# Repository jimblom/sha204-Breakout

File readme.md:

# ATSHA204 Breakout Repository
Here you'll find the hardware design files for the [SparkFun ATSHA204 Breakout](https://www.sparkfun.com/products/11551). You'll also find example Arduino code, including a library for this powerful little chip.

## What's here?
In the *hardware* directory, you'll find the Eagle design files - board and schematic - as well as a pdf version of the schematic.

In the *sha204_library* directory, you'll find the **ATSHA204 Arduino Library** as well as example code to demo what it can do. 

## What is the Atmel ATSHA204?
The Atmel ATSHA204 is an optimized authentication chip that includes a 4.5Kb EEPROM. This array can be used for storage of keys, miscellaneous read/write, read-only, password or secret data, and consumption tracking. Access to the various sections of memory can be restricted in a variety of ways and then the configuration locked to prevent changes.

Each ATSHA204 ships with a guaranteed unique 72-bit serial number. Using the cryptographic protocols supported by the chip, a host system or remote server can prove that the serial number is both authentic and not a copy. The ATSHA204 can generate high-quality random numbers and employ them for any purpose, including usage as part of the crypto protocols of this chip.

Here's a link to the [datasheet](http://www.atmel.com/Images/doc8740.pdf).

- Jim Lindblom @ SparkFun Electronics

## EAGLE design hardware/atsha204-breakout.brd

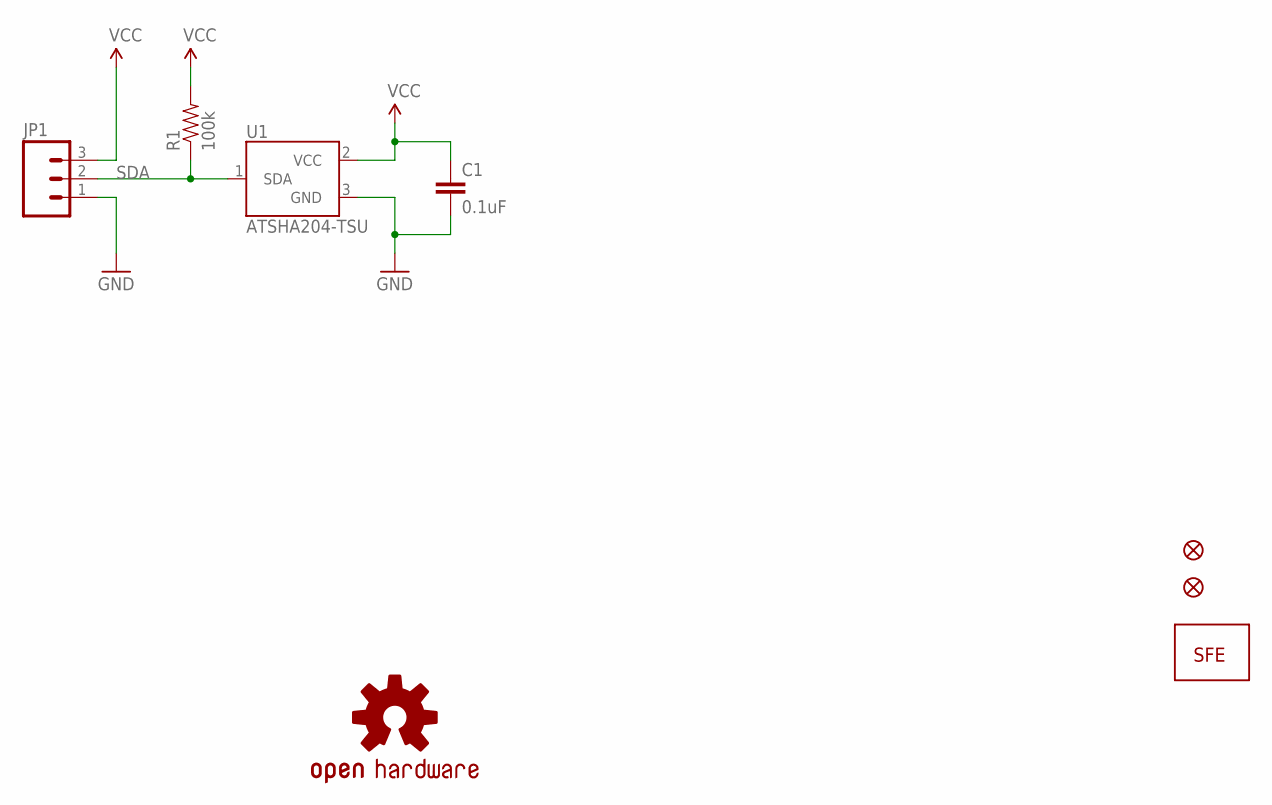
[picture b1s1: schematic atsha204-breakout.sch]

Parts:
C1: 0.1uF; 0402-CAP
JP1: M031X03_NO_SILK; 1X03_NO_SILK
JP2: LOGO-SFESK; SFE-LOGO-FLAME
JP3, JP4: FIDUCIALUFIDUCIAL; MICRO-FIDUCIAL
R1: 100k; 0402-RES
U1: ATSHA204-TSU; SOT23-3
U$1: OSHW-LOGOS; OSHW-LOGO-S

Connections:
GND: C1.2, JP1.1, U1.3 (GND)
SDA: JP1.2, R1.1, U1.1 (SDA)
VCC: C1.1, JP1.3, R1.2, U1.2 (VCC)

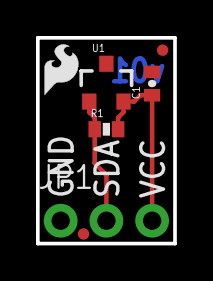
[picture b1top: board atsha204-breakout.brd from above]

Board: 2 copper layers, 7.6 x 11.4 mm, 8 parts (1 on the bottom side), 3 nets.

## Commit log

2012-11-08 Initial commit
    This is an initial working version of the sha204 library and some
    example code using it.
    Also an initial commit of the Eagle design files.
2012-11-08 Revising directory structure
    no need to navigate through all those folders to get to the code.
2012-11-09 Constructor now takes Arduino pin as parameter
    Now you can connect the ATSHA204's SDA pin to any of the Arduino's
    digital pins. The constructor now requires a parameter passed, which
    should be whatever pin you want to connect the SDA pin to.
2015-05-02 Bit Time
    8*BIT_DELAY < 37 us (datasheet / Table 7-3) http://www.atmel.com/Images/Atmel-8885-CryptoAuth-ATSHA204A-Datasheet.pdf

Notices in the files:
parts and their libraries:
SparkFun-DigitalIC: Licensing: CC v3.0 Share-Alike You are welcome to use this library for commercial purposes.
SparkFun-Aesthetics: Released under the Creative Commons
SparkFun-Aesthetics: http://creativecommons.org/licenses/by-sa/3.0
